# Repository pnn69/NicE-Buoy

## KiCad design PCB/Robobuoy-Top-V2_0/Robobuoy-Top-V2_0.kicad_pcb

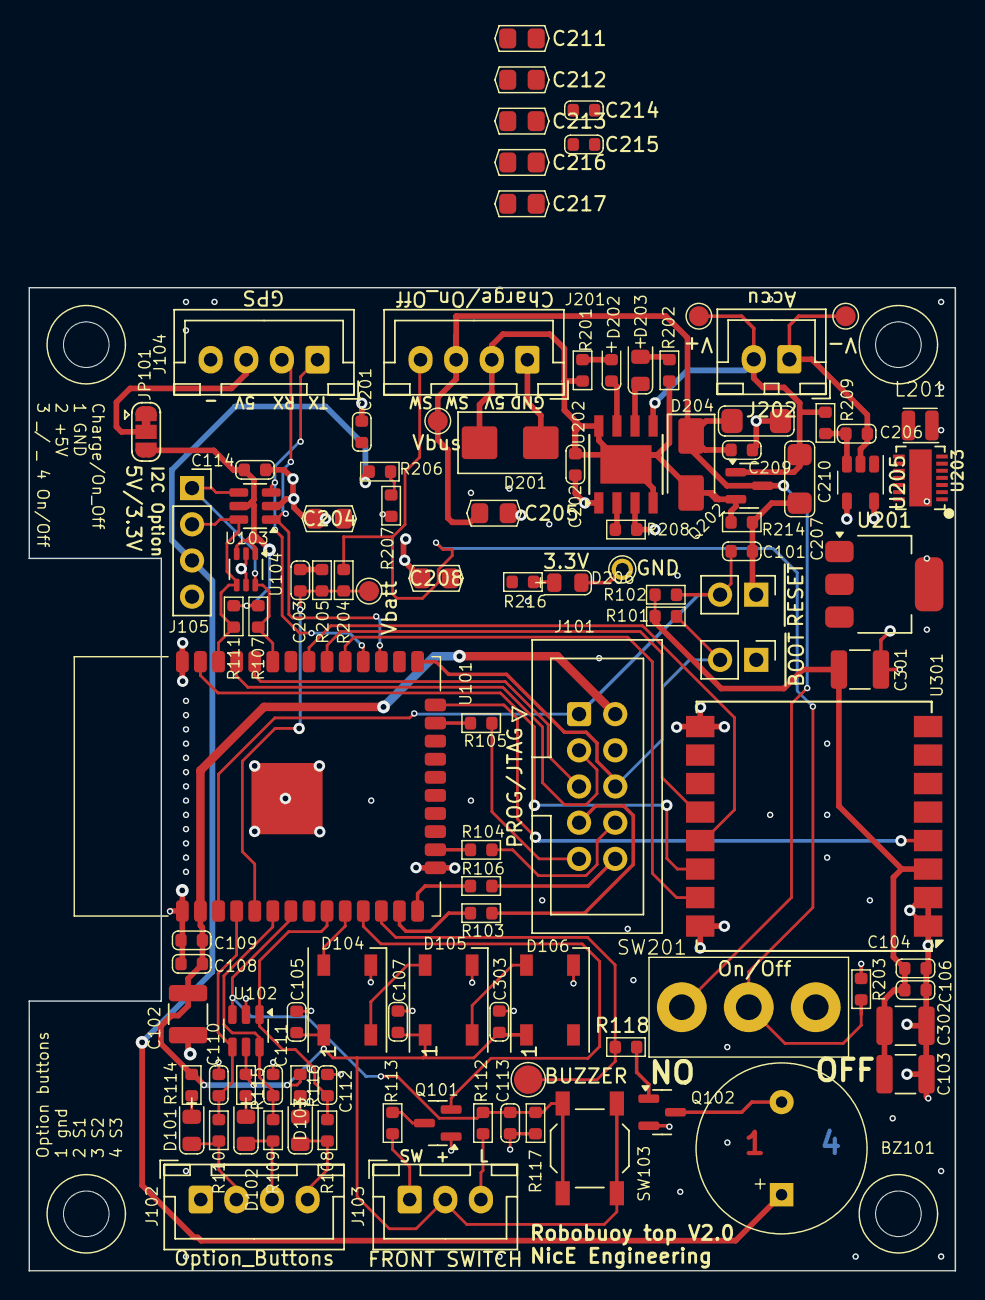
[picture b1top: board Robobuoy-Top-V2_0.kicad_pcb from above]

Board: 4 copper layers, 65.0 x 69.0 mm, 110 parts (0 on the bottom side), 63 nets.

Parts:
BZ101: Buzzer; Buzzer-12x6.5x5.2
C101, C104, C105, C106, C107, C108, C109, C110, C111, C112, C113, C114, C201, C202, C203, C206, C209, C214, C215, C303: 100n; C_0603
C102, C103, C301, C302: 100u/10V; C_1210_3225Metric
C204, C205, C208, C211, C212, C213, C216, C217: 10u/10V; C_0805
C207, C210: 4.7uF; C_1206_(1.6)
D101, D102, D103, D206: 3.3V; LED_0805
D104, D105, D106: WS2812B; LED_WS2812B_PLCC4_5.0x5.0mm_P3.2mm
D201: SMBJ5.0A; D_SMB
D202: CHRG; LED_0603
D203: READY; LED_0805
D204: B340A; D_SMA
H401, H402, H403, H404: MountingHole; NPTH_M3
J101: PROG/JTAG; IDC-Header_2x05_P2.54mm_Vertical
J102: Option_Buttons; JST_XH_B4B-XH-A_1x04_P2.50mm_Vertical
J103: FRONT SWITCH; JST_XH_B3B-XH-A_1x03_P2.50mm_Vertical
J104: GPS; JST_XH_B4B-XH-A_1x04_P2.50mm_Vertical
J105: I2C Option; PinSocket_1x04_P2.54mm_Vertical
J201: Charge/On_Off; JST_XH_B4B-XH-A_1x04_P2.50mm_Vertical
J202: Accu; JST_XH_B2B-XH-A_1x02_P2.50mm_Vertical
JP101: 5V/3.3V; SolderJumper-3_P1.3mm_Bridged12_RoundedPad1.0x1.5mm
L201: 1.5uH / 3.7A; L_2x2.5
Q101, Q202: A03401A; SOT-23
Q102: AO3400A; SOT-23
R101, R102, R117, R118, R214: 10K; R_0603
R103, R104, R105, R106, R108, R109, R110, R112, R113: 100; R_0603
R107, R111: 2.2k; R_0603
R114, R115, R116, R201, R202, R209: 1K; R_0603
R203, R207: 15K; R_0603
R204, R205, R206: 82K; R_0603
R208: 1.5K; R_0603
R216: 4.7K; R_0603
SW101: ~{BOOT}; PinHeader_1x02_P2.54mm_Vertical
SW102: ~{RESET}; PinHeader_1x02_P2.54mm_Vertical
SW103: MODE; SW_SPST_TL3342
SW201: On/Off; SS-12D10L5
TP101: BUZZER; Testpad_2
TP203: Vbatt; Testpad_1.4
TP204: V+; Testpad_1.4
TP205: V-; Testpad_1.4
TP208: GND; Testpoint_0.9x1.5
TP209: Vbus; Testpad_1.4
U101: ESP32-WROOM-32E_(visible_peripherals); ESP32-WROOM-32
U102, U103: USBLC6-4SC6; SOT-23-6
U104: LTC4311; Texas_R-PDSO-G6
U201: LM1117MP-3.3/TR; SOT-223
U202: TP4056; Diodes_PSOP-8
U203: TPS63020DSJR; QFN14_1
U205: AP6685; SOT23-5
U301: Ai-Thinker-Ra-02; Ai-Thinker-Ra-02-LoRa

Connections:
+3.3V: C102.1, C103.1, C104.1, C105.1, C106.1, C107.1, C108.1, C109.1, C114.1, C301.1, C302.1, C303.1, D104.1 (VDD), D105.1 (VDD), D106.1 (VDD), J101.2, J103.2, JP101.3 (B), R101.1, R102.1, R107.1, R111.1, R114.1, R115.1, R116.1, R216.2, SW103.2, U101.2 (VDD), U102.5 (VBUS), U103.5 (VBUS), U104.1 (VCC), U104.3 (EN), U301.3 (VDD)
+5V: BZ101.1 (+), C208.1, C211.1, C212.1, C213.1, C214.1, J105.3, JP101.1 (A), R206.1, U201.3 (VI), U203.4 (Vout), U203.5 (Vout)
/CPU/RADIO_1: U101.37 (MOSI/GPIO23), U301.14 (MOSI)
/CPU/RADIO_2: U101.31 (MISO/GPIO19), U301.13 (MISO)
/CPU/RADIO_3: U101.30 (SCK/GPIO18), U301.12 (SCK)
/CPU/RADIO_4: U101.29 (CS/GPIO5), U301.15 (~NSS)
/CPU/RADIO_5: U101.24 (D0/GPIO2), U301.4 (~RESET)
/CPU/RX_GPS: J104.2, U101.27 (RXD/GPIO16), U103.1 (I/O1)
/CPU/SCL: J105.2, R111.2, U101.36 (SCL/GPIO22), U103.6 (I/O4), U104.4 (BUS2)
/CPU/SDA: J105.1, R107.2, U101.33 (SDA/GPIO21), U103.4 (I/O3), U104.6 (BUS1)
/CPU/TX_GPS: J104.1, U101.28 (TXD/GPIO17), U103.3 (I/O2)
/CPU/Vbatt: C203.1, R204.2, R205.1, TP203.1, U101.5 (GPIO39)
/CPU/Vgps: J104.3, JP101.2 (C)
BUTTON: C113.1, R112.1, R117.1, SW103.1, U101.7 (GPIO35), U102.3 (I/O2)
BUTTON1: C110.1, R110.1, U101.4 (GPIO36), U102.4 (I/O3)
BUTTON2: C111.1, R109.1, U101.6 (GPIO34), U102.6 (I/O4)
BUTTON3: C112.1, R108.1, U101.9 (GPIO33), U102.1 (I/O1)
BUTTON_LIGHT: Q101.2 (G), U101.11 (GPIO26)
BUZZER: R118.1, TP101.1, U101.12 (GPIO27)
DR0: J101.6, R101.2, SW101.2, U101.25 (BOOT/GPIO0)
EN: C101.1, J101.1, R102.2, SW102.2, U101.3 (CHIP_PU/EN)
Enable: J201.4, R203.1, R204.1, SW201.2, U203.12 (EN)
GND: C101.2, C102.2, C103.2, C104.2, C105.2, C106.2, C107.2, C108.2, C109.2, C110.2, C111.2, C112.2, C113.2, C114.2, C201.2, C202.2, C203.2, C204.2, C205.2, C207.2, C208.2, C209.2, C210.2, C211.2, C212.2, C213.2, C214.2, C215.2, C216.2, C217.2, C301.2, C302.2, C303.2, D104.3 (VSS), D105.3 (VSS), D106.3 (VSS), D201.2 (A2), D206.1 (K), J101.4, J102.1, J104.4, J105.4, J201.1, Q101.1 (D), Q102.2 (S), R117.2, R203.2, R205.2, R207.2, R208.2, R214.2, SW101.1, SW102.1, TP208.1, U101.1 (GND), U101.15 (GND), U101.38 (GND), U101.39 (GND), U102.2 (GND), U103.2 (GND), U104.2 (GND), U104.5 (GND), U201.1 (GND), U202.1 (TEMP), U202.3 (GND), U203.2 (GND), U203.15 (PGND), U205.4 (VM), U205.5 (VM), U301.1 (GND), U301.2 (GND), U301.9 (GND), U301.16 (GND)
LEDS: D104.4 (DIN), U101.10 (GPIO25)
MTCK: R104.2, U101.16 (MTCK/MOSI/D3/GPIO13)
MTDI: R106.2, U101.14 (MTDI/MISO/D2/GPIO12)
MTDO: R105.2, U101.23 (MTDO/CS/CMD/GPIO15)
MTMS: R103.2, U101.13 (MTMS/SCK/CLK/GPIO14)
unnamed: BZ101.2 (-), Q102.3 (D)
unnamed: D101.2 (A), R114.2
unnamed: D101.1 (K), J102.2, R110.2
unnamed: D102.2 (A), R115.2
unnamed: D102.1 (K), J102.3, R109.2
unnamed: D103.2 (A), R116.2
unnamed: D103.1 (K), J102.4, R108.2
unnamed: D104.2 (DOUT), D105.4 (DIN)
unnamed: D105.2 (DOUT), D106.4 (DIN)
unnamed: D202.2 (A), R201.2
unnamed: D202.1 (K), U202.7 (~CHRG)
unnamed: D203.2 (A), R202.1
unnamed: D203.1 (K), U202.6 (~STDBY)
unnamed: D206.2 (A), R216.1
unnamed: J101.7, R103.1
unnamed: J101.8, R104.1
unnamed: J101.9, R105.1
unnamed: J101.10, R106.1
unnamed: J103.1, R113.2
unnamed: J103.3, R112.2
unnamed: C206.2, J202.1, TP205.1, U205.2 (GND)
unnamed: C207.1, J202.2, Q202.1 (D), R209.1, TP204.1, U202.5 (BAT)
unnamed: L201.1, U203.8 (L1), U203.9 (L1)
unnamed: L201.2, U203.6 (L2), U203.7 (L2)
unnamed: Q101.3 (S), R113.1
unnamed: Q102.1 (G), R118.2
unnamed: R206.2, R207.1
unnamed: C215.1, C216.1, C217.1, U201.2 (VO)
unnamed: R208.1, U202.2 (PROG)
unnamed: C201.1, U203.1 (Vina), U203.13 (PS/SYNC)
unnamed: C206.1, R209.2, U205.3 (VDD)
PAD: C202.1, D201.1 (A1), D204.2 (A), J201.2, Q202.2 (G), R201.1, R202.2, R214.1, U202.4 (Vcc), U202.8 (CE), U202.9 (PAD)
RX: J101.5, U101.34 (RXD/GPIO3)
TX: J101.3, U101.35 (TXD/GPIO1)
VBUS: C204.1, C205.1, C209.1, C210.1, D204.1 (K), J201.3, Q202.3 (S), SW201.1, TP209.1, U203.10 (Vin), U203.11 (Vin)

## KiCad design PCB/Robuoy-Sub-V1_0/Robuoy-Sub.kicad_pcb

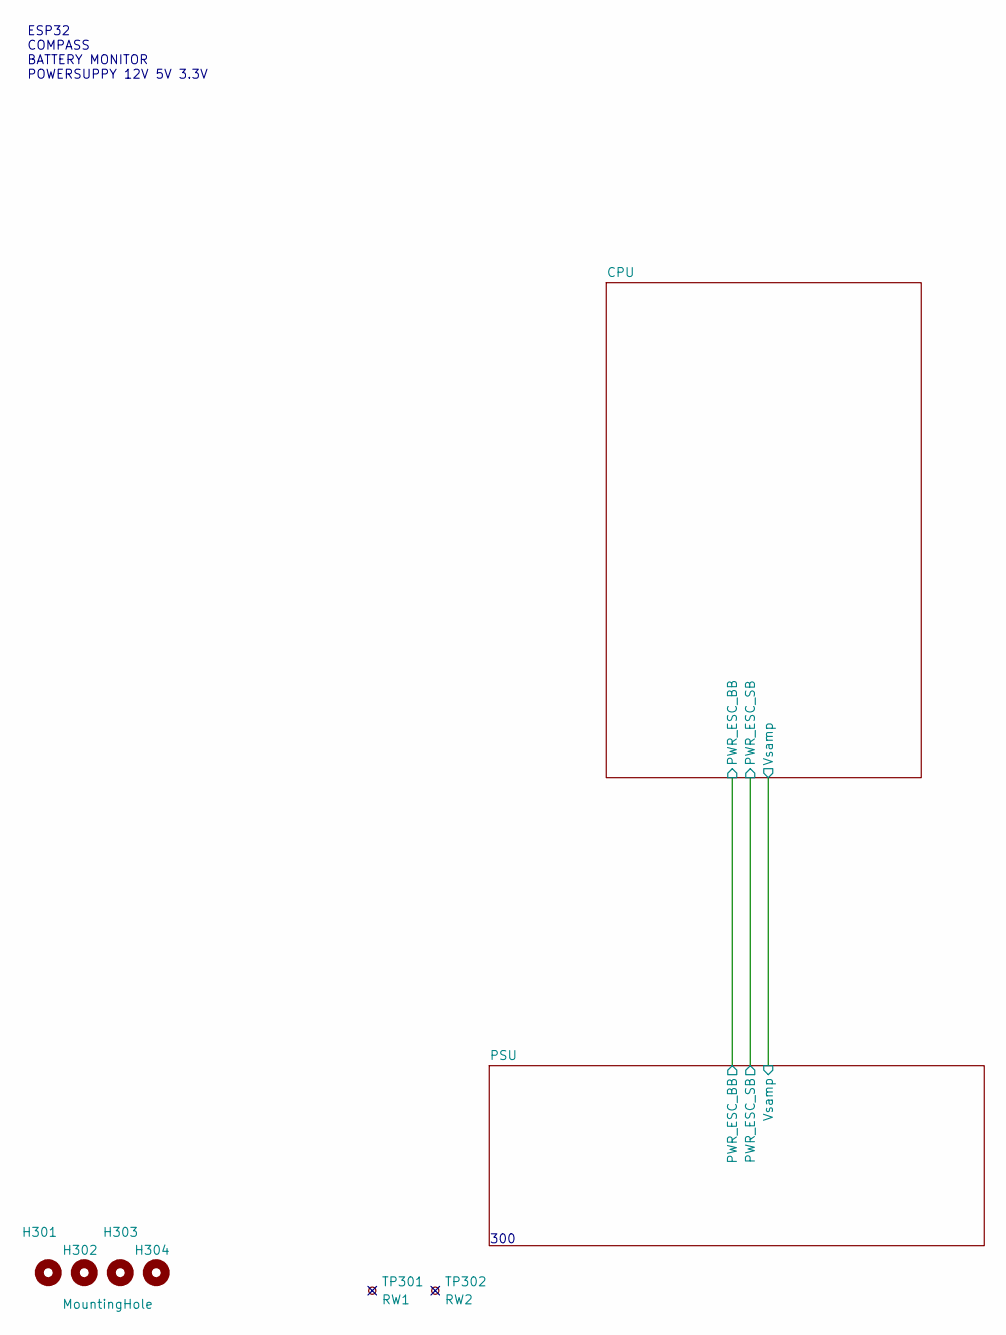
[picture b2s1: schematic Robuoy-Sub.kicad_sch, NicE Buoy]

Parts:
H301, H302, H303, H304: MountingHole; NPTH_M3
TP301: RW1; ReworkPins
TP302: RW2; ReworkPins

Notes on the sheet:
300
ESP32 COMPASS BATTERY MONITOR POWERSUPPY 12V 5V 3.3V

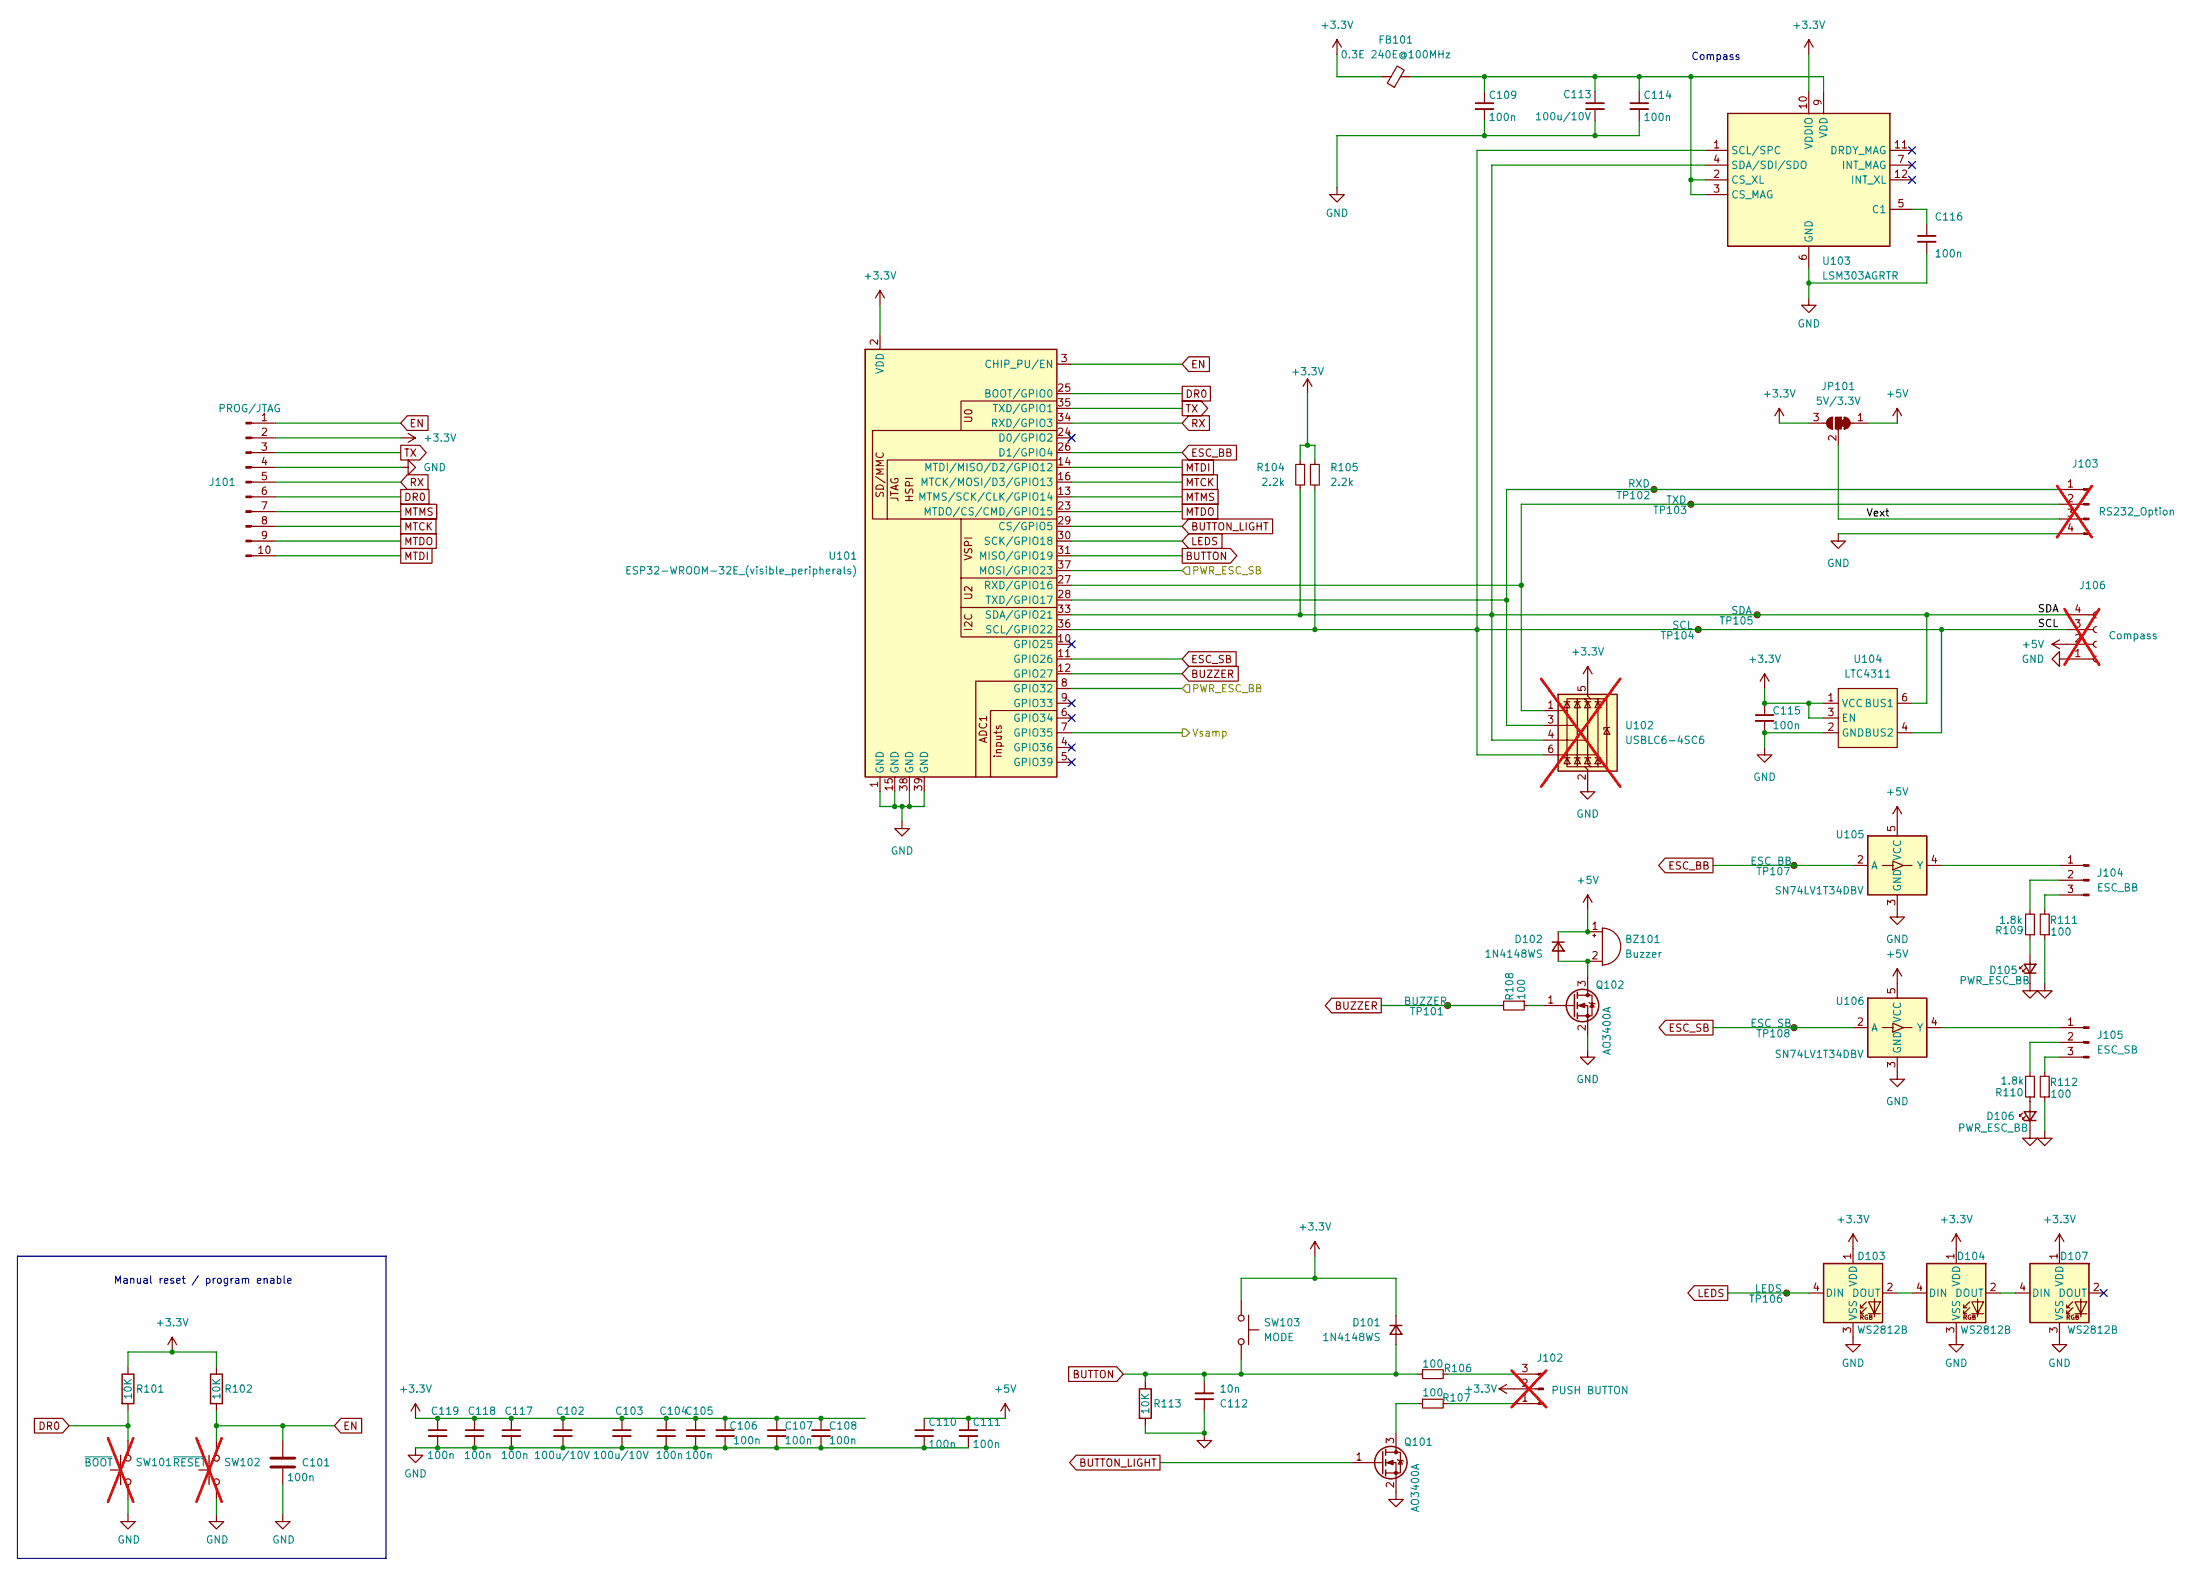
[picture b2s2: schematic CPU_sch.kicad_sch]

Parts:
BZ101: Buzzer; Buzzer-12x6.5x5.2; LCSC C968749
C101, C104, C105, C106, C107, C108, C109, C110, C111, C114, C115, C116, C117, C118, C119: 100n; C_0603; LCSC C14663
C102, C103, C113: 100u/10V; C_1210_3225Metric; LCSC C23742
C112: 10n; C_0603; LCSC C57112
D101, D102: 1N4148WS; D_SOD-323_1.8x1.4x1.15; LCSC C2128
D103, D104, D107: WS2812B; LED_WS2812B_PLCC4_5.0x5.0mm_P3.2mm; LCSC C2843785
D105, D106: PWR_ESC_BB; LED_0603_1608Metric; LCSC C2286
FB101: 0.3E 240E@100MHz; L_0805_(1.2); LCSC C2941558
J101: PROG/JTAG; IDC-Header_2x05_P2.54mm_Vertical; LCSC C5665
J102: PUSH BUTTON; JST_XH_B3B-XH-A_1x03_P2.50mm_Vertical; LCSC C5341202; not fitted
J103: RS232_Option; PinSocket_1x04_P2.54mm_Vertical; LCSC C2718488; not fitted
J104: ESC_BB; JST_XH_B3B-XH-A_1x03_P2.50mm_Vertical; LCSC C5341202
J105: ESC_SB; JST_XH_B3B-XH-A_1x03_P2.50mm_Vertical; LCSC C5341202
J106: Compass; JST_XH_B4B-XH-A_1x04_P2.50mm_Vertical; LCSC C5341203; not fitted
JP101: 5V/3.3V; SolderJumper-3_P1.3mm_Bridged12_RoundedPad1.0x1.5mm
Q101, Q102: AO3400A; SOT-23; LCSC C20917
R101, R102, R113: 10K; R_0603; Farnell 2331736
R104, R105: 2.2k; R_0603; LCSC C4190
R106, R107, R108, R111, R112: 100; R_0603; LCSC C22775
R109, R110: 1.8k; R_0603; LCSC C4177
SW101: ~{BOOT}; PinHeader_1x02_P2.54mm_Vertical; not fitted
SW102: ~{RESET}; PinHeader_1x02_P2.54mm_Vertical; not fitted
SW103: MODE; SW_SPST_TL3342; LCSC C318884
TP101: BUZZER; Testpad_1
TP102: RXD; Testpad_1
TP103: TXD; Testpad_1
TP104: SCL; Testpad_1
TP105: SDA; Testpad_1
TP106: LEDS; Testpad_1
TP107: ESC_BB; Testpad_1
TP108: ESC_SB; Testpad_1
U101: ESP32-WROOM-32E_(visible_peripherals); ESP32-WROOM-32; LCSC C82899
U102: USBLC6-4SC6; SOT-23-6; LCSC C5197386; not fitted
U103: LSM303AGRTR; LGA-12_2x2mm_P0.5mm; LCSC C126671
U104: LTC4311; Texas_R-PDSO-G6; LCSC C580856
U105, U106: SN74LV1T34DBV; SOT-23-5; LCSC C100024

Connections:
+3.3V: C102.1, C103.1, C104.1, C105.1, C106.1, C107.1, C108.1, C115.1, C117.1, C118.1, C119.1, D101.1 (K), D103.1 (VDD), D104.1 (VDD), D107.1 (VDD), FB101.1, J101.2, J102.2, JP101.3 (B), R101.1, R102.1, R104.1, R105.1, SW103.2, U101.2 (VDD), U102.5 (VBUS), U103.10 (VDDIO), U104.1 (VCC), U104.3 (EN); also elsewhere on the board
+5V: BZ101.1 (+), C110.1, C111.1, D102.1 (K), J106.2, JP101.1 (A), U105.5 (VCC), U106.5 (VCC); also elsewhere on the board
/CPU/PWR_ESC_BB: U101.8 (GPIO32); also elsewhere on the board
/CPU/PWR_ESC_SB: U101.37 (MOSI/GPIO23); also elsewhere on the board
/CPU/SCL: J106.3, R105.2, TP104.1, U101.36 (SCL/GPIO22), U102.6 (I/O4), U103.1 (SCL/SPC), U104.4 (BUS2)
/CPU/SDA: J106.4, R104.2, TP105.1, U101.33 (SDA/GPIO21), U102.4 (I/O3), U103.4 (SDA/SDI/SDO), U104.6 (BUS1)
/CPU/Vext: J103.3, JP101.2 (C)
/CPU/Vsamp: U101.7 (GPIO35); also elsewhere on the board
BUTTON: C112.2, D101.2 (A), R106.1, R113.1, SW103.1, U101.31 (MISO/GPIO19)
BUTTON_LIGHT: Q101.1 (G), U101.29 (CS/GPIO5)
BUZZER: R108.2, TP101.1, U101.12 (GPIO27)
DR0: J101.6, R101.2, SW101.2, U101.25 (BOOT/GPIO0)
EN: C101.1, J101.1, R102.2, SW102.2, U101.3 (CHIP_PU/EN)
ESC_BB: TP107.1, U101.26 (D1/GPIO4), U105.2 (A)
ESC_SB: TP108.1, U101.11 (GPIO26), U106.2 (A)
GND: C101.2, C102.2, C103.2, C104.2, C105.2, C106.2, C107.2, C108.2, C109.2, C110.2, C111.2, C112.1, C113.2, C114.2, C115.2, C116.2, C117.2, C118.2, C119.2, D103.3 (VSS), D104.3 (VSS), D105.1 (K), D106.1 (K), D107.3 (VSS), J101.4, J103.4, J106.1, Q101.2 (S), Q102.2 (S), R111.1, R112.1, R113.2, SW101.1, SW102.1, U101.1 (GND), U101.15 (GND), U101.38 (GND), U101.39 (GND), U102.2 (GND), U103.6 (GND), U103.8 (GND), U104.2 (GND), U104.5 (GND), U105.3 (GND), U106.3 (GND); also elsewhere on the board
LEDS: D103.4 (DIN), TP106.1, U101.30 (SCK/GPIO18)
MTCK: J101.8, U101.16 (MTCK/MOSI/D3/GPIO13)
MTDI: J101.10, U101.14 (MTDI/MISO/D2/GPIO12)
MTDO: J101.9, U101.23 (MTDO/CS/CMD/GPIO15)
MTMS: J101.7, U101.13 (MTMS/SCK/CLK/GPIO14)
unnamed: BZ101.2 (-), D102.2 (A), Q102.3 (D)
unnamed: D103.2 (DOUT), D104.4 (DIN)
unnamed: D104.2 (DOUT), D107.4 (DIN)
unnamed: D105.2 (A), R109.1
unnamed: D106.2 (A), R110.1
unnamed: J102.1, R107.2
unnamed: J102.3, R106.2
unnamed: J103.1, TP102.1, U101.28 (TXD/GPIO17), U102.3 (I/O2)
unnamed: J103.2, TP103.1, U101.27 (RXD/GPIO16), U102.1 (I/O1)
unnamed: J104.1, U105.4 (Y)
unnamed: J104.2, R109.2
unnamed: J104.3, R111.2
unnamed: J105.1, U106.4 (Y)
unnamed: J105.2, R110.2
unnamed: J105.3, R112.2
unnamed: Q101.3 (D), R107.1
unnamed: Q102.1 (G), R108.1
unnamed: C116.1, U103.5 (C1)
unnamed: C109.1, C113.1, C114.1, FB101.2, U103.2 (CS_XL), U103.3 (CS_MAG), U103.9 (VDD)
RX: J101.5, U101.34 (RXD/GPIO3)
TX: J101.3, U101.35 (TXD/GPIO1)

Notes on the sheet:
Compass
Manual reset / program enable

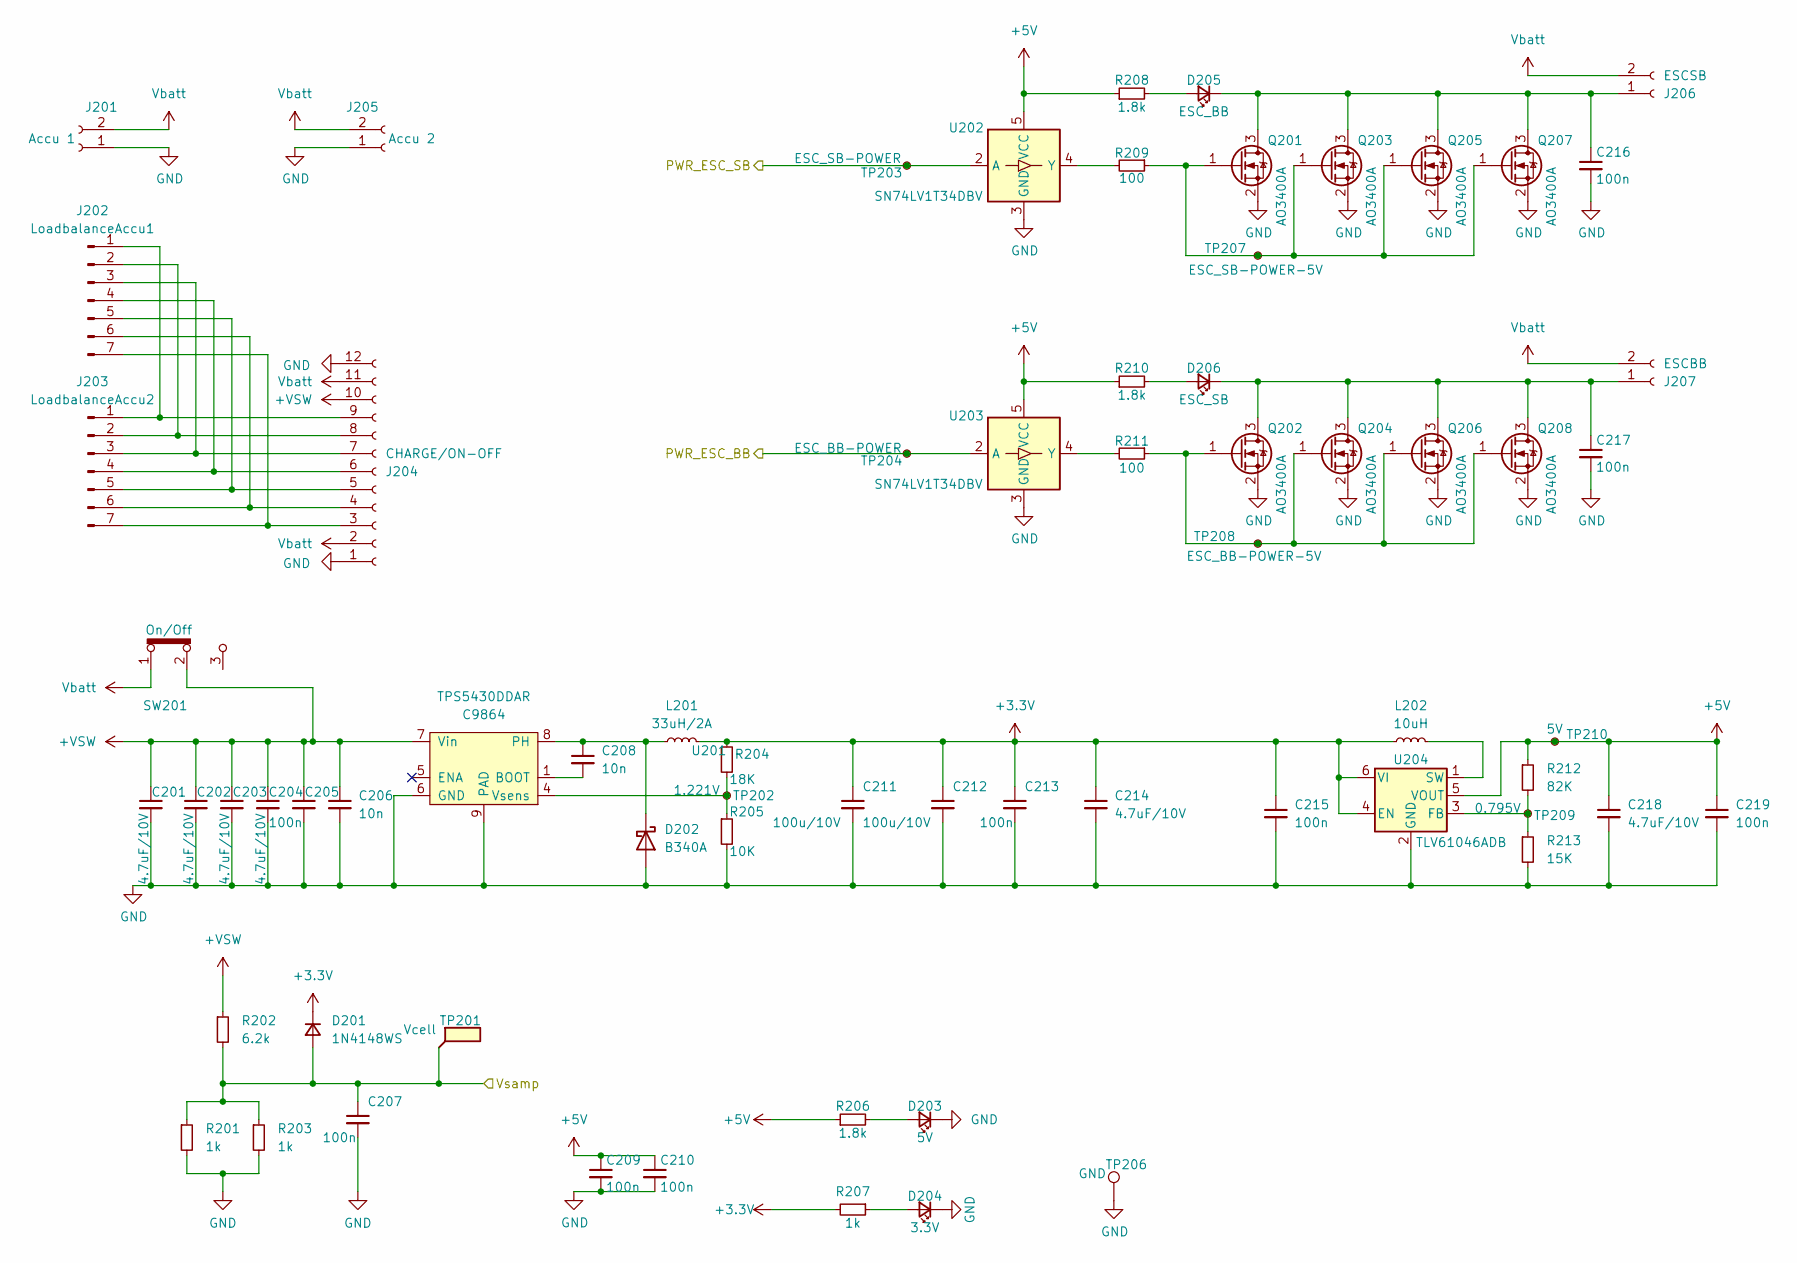
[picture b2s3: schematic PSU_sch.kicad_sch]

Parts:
C201, C202, C203, C204, C214, C218: 4.7uF/10V; C_1206_(1.6); LCSC C29823
C205, C207, C209, C210, C213, C215, C216, C217, C219: 100n; C_0603; LCSC C14663
C206, C208: 10n; C_0603; LCSC C57112
C211, C212: 100u/10V; C_1210_3225Metric; LCSC C23742
D201: 1N4148WS; D_SOD-323_1.8x1.4x1.15; LCSC C2128
D202: B340A; D_SMA; LCSC C85098
D203: 5V; LED_0805; LCSC C2297
D204: 3.3V; LED_0805; LCSC C2297
D205: ESC_BB; LED_0805; LCSC C2297
D206: ESC_SB; LED_0805; LCSC C2297
J201: Accu 1; AMASS_XT60-M_1x02_P7.20mm_Vertical; LCSC C98733
J202: LoadbalanceAccu1; JST_XH_B7B-XH-A_1x07_P2.50mm_Vertical; LCSC C5341206
J203: LoadbalanceAccu2; JST_XH_B7B-XH-A_1x07_P2.50mm_Vertical; LCSC C5341206
J204: CHARGE/ON-OFF; T4140012121000; LCSC C319012
J205: Accu 2; AMASS_XT60-M_1x02_P7.20mm_Vertical; LCSC C98733
J206: ESCSB; AMASS_XT60-F_1x02_P7.20mm_Vertical; LCSC C98734
J207: ESCBB; AMASS_XT60-F_1x02_P7.20mm_Vertical; LCSC C98734
L201: 33uH/2A; L_6.6x7.0mm; LCSC C177245
L202: 10uH; FTC252012S; LCSC C5832376
Q201, Q202, Q203, Q204, Q205, Q206, Q207, Q208: AO3400A; SOT-23; LCSC C20917
R201, R203, R207: 1k; R_0603; LCSC C21190
R202: 6.2k; R_0603; LCSC C25804
R204: 18K; R_0603; LCSC C25810
R205: 10K; R_0603; LCSC C25804
R206: 1.8k; R_0603
R208, R210: 1.8k; R_0603; LCSC C4177
R209, R211: 100; R_0603; LCSC C22775
R212: 82K; R_0603; LCSC C23254
R213: 15K; R_0603; LCSC C22809
SW201: On/Off; SS-12D10L5; LCSC C319012
TP201: Vcell; Testpad_1
TP202: 1.221V; Testpad_1
TP203: ESC_SB-POWER; Testpad_1
TP204: ESC_BB-POWER; Testpad_1
TP206: GND; TestPoint_Loop_D2.54mm_Drill1.5mm_Beaded
TP207: ESC_SB-POWER-5V; Testpad_1
TP208: ESC_BB-POWER-5V; Testpad_1
TP209: 0.795V; Testpad_1
TP210: 5V; Testpad_1
U201: TPS5430DDAR; HTSOP-8-1EP_3.9x4.9mm_P1.27mm_EP2.4x3.2mm_ThermalVias; LCSC C9864
U202, U203: SN74LV1T34DBV; SOT-23-5; LCSC C100024
U204: TLV61046ADB; SOT-23-6; LCSC C464815

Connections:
+3.3V: C211.1, C212.1, C213.1, C214.1, C215.1, D201.1 (K), L201.2, L202.1, R204.1, R207.2, U204.4 (EN), U204.6 (VI); also elsewhere on the board
+5V: C209.1, C210.1, C218.1, C219.1, R206.1, R208.1, R210.1, R212.1, TP210.1, U202.5 (VCC), U203.5 (VCC), U204.5 (VOUT); also elsewhere on the board
+VSW: C201.1, C202.1, C203.1, C204.1, C205.1, C206.1, J204.10, R202.1, SW201.2, U201.7 (Vin)
/CPU/PWR_ESC_BB: TP204.1, U203.2 (A); also elsewhere on the board
/CPU/PWR_ESC_SB: TP203.1, U202.2 (A); also elsewhere on the board
/CPU/Vsamp: C207.1, D201.2 (A), R201.1, R202.2, R203.1, TP201.1; also elsewhere on the board
GND: C201.2, C202.2, C203.2, C204.2, C205.2, C206.2, C207.2, C209.2, C210.2, C211.2, C212.2, C213.2, C214.2, C215.2, C216.2, C217.2, C218.2, C219.2, D202.2 (A), D203.1 (K), D204.1 (K), J201.1, J204.1, J204.12, J205.1, Q201.2 (S), Q202.2 (S), Q203.2 (S), Q204.2 (S), Q205.2 (S), Q206.2 (S), Q207.2 (S), Q208.2 (S), R201.2, R203.2, R205.2, R213.2, TP206.1, U201.6 (GND), U201.9 (PAD), U202.3 (GND), U203.3 (GND), U204.2 (GND); also elsewhere on the board
unnamed: C208.1, D202.1 (K), L201.1, U201.8 (PH)
unnamed: D203.2 (A), R206.2
unnamed: D204.2 (A), R207.1
unnamed: D205.2 (A), R208.2
unnamed: C216.1, D205.1 (K), J206.1, Q201.3 (D), Q203.3 (D), Q205.3 (D), Q207.3 (D)
unnamed: D206.2 (A), R210.2
unnamed: C217.1, D206.1 (K), J207.1, Q202.3 (D), Q204.3 (D), Q206.3 (D), Q208.3 (D)
unnamed: J202.1, J203.1, J204.9
unnamed: J202.2, J203.2, J204.8
unnamed: J202.3, J203.3, J204.7
unnamed: J202.4, J203.4, J204.6
unnamed: J202.5, J203.5, J204.5
unnamed: J202.6, J203.6, J204.4
unnamed: J202.7, J203.7, J204.3
unnamed: Q201.1 (G), Q203.1 (G), Q205.1 (G), Q207.1 (G), R209.1, TP207.1
unnamed: Q202.1 (G), Q204.1 (G), Q206.1 (G), Q208.1 (G), R211.1, TP208.1
unnamed: C208.2, U201.1 (BOOT)
unnamed: R204.2, R205.1, TP202.1, U201.4 (Vsens)
unnamed: R209.2, U202.4 (Y)
unnamed: R211.2, U203.4 (Y)
unnamed: R212.2, R213.1, TP209.1, U204.3 (FB)
unnamed: L202.2, U204.1 (SW)
Vbatt: J201.2, J204.2, J204.11, J205.2, J206.2, J207.2, SW201.1

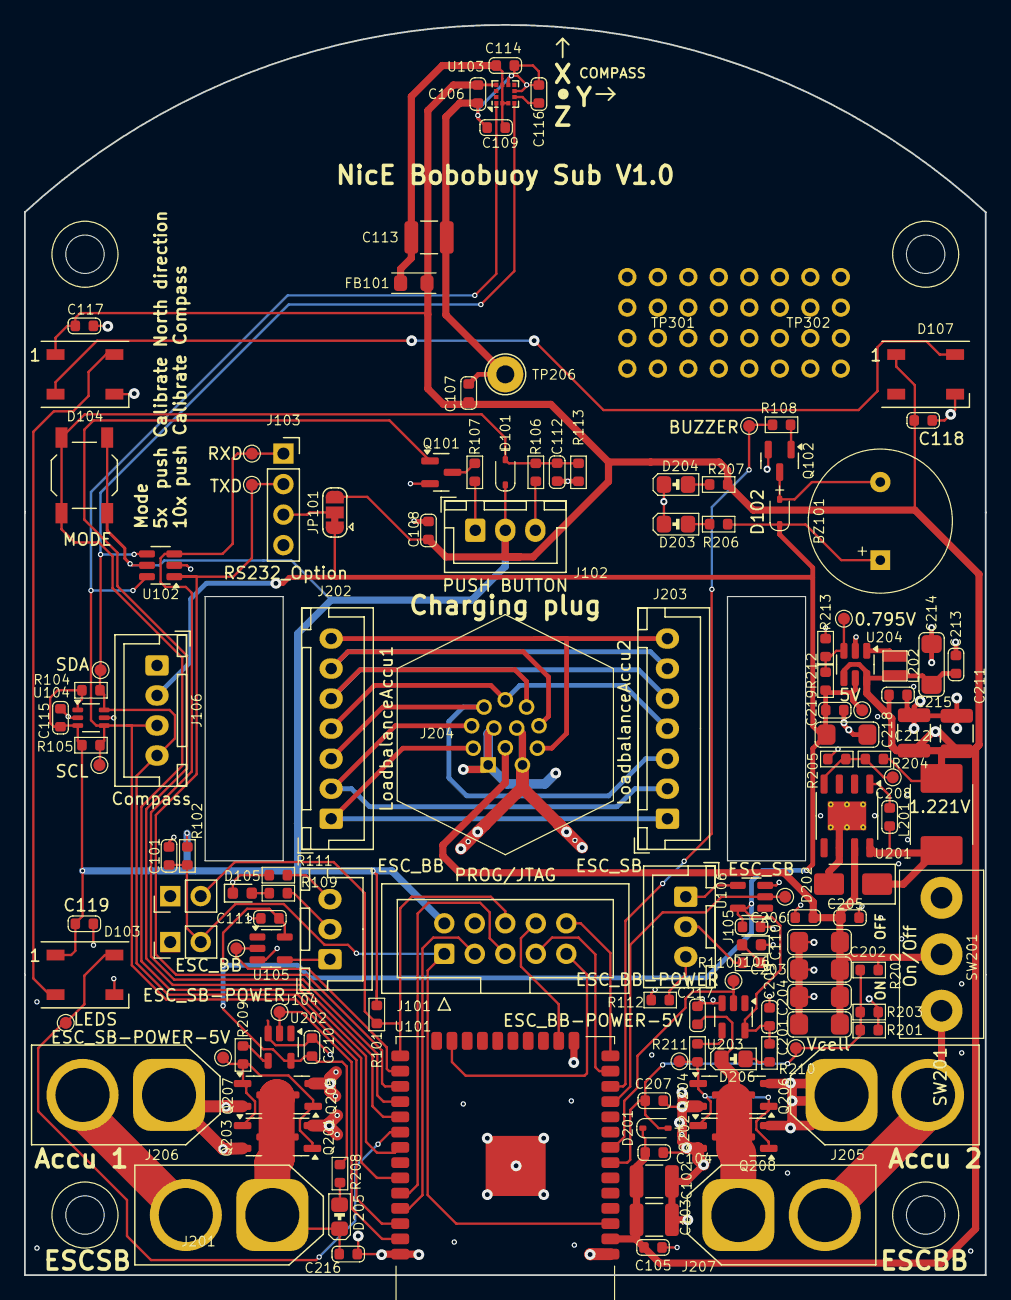
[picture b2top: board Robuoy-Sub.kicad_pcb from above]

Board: 4 copper layers, 80.0 x 104.1 mm, 141 parts (0 on the bottom side), 66 nets.

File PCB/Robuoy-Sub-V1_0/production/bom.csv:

Designator,Footprint,Quantity,Value,LCSC Part #
"C101, C104, C105, C106, C107, C108, C109, C110, C111, C113, C205, C207, C209, C210, C213, C215, C216, C217, C219",C_0603,19,100n,C14663
"C102, C103, C211, C212",1210,4,100u/16V,C90143
"C112, C206, C208",C_0603,3,10n,C57112
"C201, C202, C203, C204, C214, C218",C_1206_(1.6),6,4.7uF/10V,C29823
"D101, D201",D_SOD-123_2.85x1.8x1.3,2,SM4007PL,C64898
"D102, D103, D106",LED_WS2812B_PLCC4_5.0x5.0mm_P3.2mm,3,WS2812B,C2843785
"D104, D105",0603,2,PWR_ESC_BB,C2286
D202,D_SMA,1,B340A,C85098
D203,LED_0805,1,5V,C2297
D204,LED_0805,1,3.3V,C2297
D205,LED_0805,1,ESC_BB,C2297
D206,LED_0805,1,ESC_SB,C2297
J101,IDC-Header_2x05_P2.54mm_Vertical,1,PROG/JTAG,C5665
J102,JST_XH_B3B-XH-A_1x03_P2.50mm_Vertical,1,TO PUSH BUTTON,C161870
J103,PinHeader_1x03_P2.54mm_Vertical,1,ESC_BB,C161870
J104,PinHeader_1x03_P2.54mm_Vertical,1,ESC_SB,C161870
J105,JST_XH_B4B-XH-A_1x04_P2.50mm_Vertical,1,RS232_Option,C98734
J106,Header_1x04_P2.54_Male,1,Compass,C144395
J201,AMASS_XT60-M_1x02_P7.20mm_Vertical,1,Accu,C98733
J202,JST_XH_B7B-XH-A_1x07_P2.50mm_Vertical,1,LoadbalanceAccu1,C5341206
J203,JST_XH_B7B-XH-A_1x07_P2.50mm_Vertical,1,LoadbalanceAccu2,C5341206
J204,JST_XH_B10B-XH-A_1x10_P2.50mm_Vertical,1,Conn_01x10,C7434315
J205,AMASS_XT60-F_1x02_P7.20mm_Vertical,1,PWR_Charger,C98733
J206,JST_XH_B7B-XH-A_1x07_P2.50mm_Vertical,1,LoadbalanceCharger,C5341206
J207,AMASS_XT60-F_1x02_P7.20mm_Vertical,1,ESCSB,C98734
J208,AMASS_XT60-F_1x02_P7.20mm_Vertical,1,ESCBB,C98734
JP101,SolderJumper-3_P1.3mm_Bridged12_RoundedPad1.0x1.5mm,1,5V/3.3V,
L201,L_6.6x7.0mm,1,33uH/2A,C177245
L202,FTC252012S,1,10uH,C5832376
"Q101, Q201, Q202, Q203, Q204, Q205, Q206, Q207, Q208",SOT-23,9,AO3400A,C20917
"R101, R102, R205",R_0603,3,10K,C25804
"R103, R104, R105, R106, R110, R111",R_0603,6,100,C22775
R107,R_0603,1,820,C21190
"R108, R109",R_0603,2,2.2k,C21190
"R112, R113, R208, R209",R_0603,4,1.8k,C4177
"R201, R203, R207",R_0603,3,1k,C21190
R202,R_0603,1,6.2k,C25804
R204,R_0603,1,18K,C25810
R206,R_0603,1,1.8k,
R210,R_0603,1,82K,C23254
R211,R_0603,1,15K,C22809
SW201,SS-12D10L5,1,SS-12D11-G050/On-Off,C319012
TP201,Testpoint_0.9x1.5,1,Vcell,
TP202,Testpoint_0.9x1.5,1,GND,
TP203,Testpoint_0.9x1.5,1,0.795V,
TP204,Testpoint_0.9x1.5,1,5V,
U101,ESP32-WROOM-32,1,ESP32-WROOM-32E_(visible_peripherals),C82899
U102,SOT-23-6,1,USBLC6-4SC6,C5197386
U103,Texas_R-PDSO-G6,1,LTC4311,C580856
"U104, U105, U202, U203",SOT-23-5,4,SN74LV1T34DBV,C100024
U201,HTSOP-8-1EP_3.9x4.9mm_P1.27mm_EP2.4x3.2mm_ThermalVias,1,TPS5430DDAR,C9864
U204,SOT-23-6,1,TLV61046ADB,C464815
